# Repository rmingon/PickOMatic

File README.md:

# PickOMatic Motion Controller

Custom motion-control PCB for the PickOMatic pick-and-place toolchain. The board centers on an ATmega2560 (16 MHz) and exposes everything needed to drive the mechanics of a multi-head component placer: coordinated stepper motion, pneumatic handling, lighting, endstop monitoring, and USB connectivity for streaming G-code.

## Repository Layout

- `hardware/` – KiCad 8 project: schematic, PCB, fabrication outputs, and backups.
- `schematic.png` / `pcb.png` / `3D.png` – quick previews of the current design.

Open the KiCad project (`hardware/hardware.kicad_pro`) to inspect or modify the schematic/PCB.

## Hardware Highlights

| Function              | Implementation                                                                                                                             |
| --------------------- | ------------------------------------------------------------------------------------------------------------------------------------------ |
| MCU                   | ATmega2560 @ 16 MHz with a full 5 V I/O bank exposed for motion, sensors, and auxiliary loads.                                             |
| Programming           | Standard 6-pin AVR-ISP header for bootloader bring-up, plus an onboard CH340C USB-UART for firmware uploads and runtime G-code/telemetry.  |
| Axis control          | Five primary stepper channels (2×X, 2×Y, 1×Z) plus two auxiliary stepper channels dedicated to the dual picker heads.                      |
| Vertical compliance   | Three hobby-servo outputs cooperate with the Z axis so each picker head can adjust nozzle height independently (fine pitch vs bulk parts). |
| Pneumatics & lighting | High-side driver for the vacuum/air pump and relay output for the inspection light that assists the vision camera.                         |
| Endstops              | Five limit-switch inputs routed to PCINT lines so firmware can react immediately to any axis stop without polling latency.                 |

## Connectors & Loads

- **Power** – The digital domain remains at 5 V; provide the motor/lighting voltages required by your external drivers (consult the schematic to confirm connector pinouts and allowable current).
- **Steppers** – Eight pairs of STEP/DIR outputs let you interface with typical plug-in drivers (A4988, DRV8825, TMC series). Wire the two X and two Y channels to the corresponding gantry motors so firmware can keep them phase-aligned.
- **Servos** – Three 3-pin headers (signal/5 V/GND) drive standard RC servos for nozzle tilt or compliance adjustments.
- **Vacuum & light** – The pump driver is sized for continuous duty vacuum pumps; the relay contact can switch the illumination supply for the fiducial/alignment camera.
- **Endstops** – Use normally-closed switches whenever possible; the PCINT implementation catches interruptions even while the MCU is servicing other tasks.

Refer to `hardware.kicad_sch` for exact connector references, fuse ratings, and any net labels that tie into your firmware pin map.

## Getting Started

1. **Inspect the PCB** – Open the KiCad design and verify clearances, mounting, and connector orientation against your mechanical assembly.
2. **Assemble & power** – Populate the MCU, CH340C, power regulators, and the motion-control connectors. Bring up the board on a bench supply; check that 5 V and any motor rails stay within tolerance under load.
3. **Flash the bootloader** – Use an AVR ISP (e.g., USBasp, Atmel-ICE) on the 6-pin header:

   ```bash
   avrdude -c usbasp -p m2560 -U flash:w:optiboot_atmega2560.hex
   ```

4. **Deploy firmware** – Upload your motion firmware (Marlin, grbl-Mega, custom G-code interpreter) over the CH340C virtual COM port, typically at 115200 baud.
5. **Verify I/O** – Exercise each stepper, servo, and pneumatic output with low-current loads before connecting the actual actuators. Confirm that every endstop triggers in firmware by manually toggling the switches.
6. **Integrate with the PickOMatic toolchain** – Point your host software (Python scripts, OpenPnP, etc.) at the CH340C serial port and stream G-code or custom motion commands.

## Firmware Notes

- **Stepper pairing** – Configure your firmware so the twin X and Y motors share motion planners but can be trammed independently (use dual endstops or sensorless homing if supported).
- **PCINT handling** – Enable pin-change interrupts for the five limit inputs to guarantee hard-stop reactions regardless of motion planner load.
- **Auxiliary steppers** – Treat the dual picker-head steppers as independent “U” and “V” axes or bind them to tool-change macros to orient the nozzles before pick/place moves.
- **Servo timing** – The ATmega2560 has enough timers to dedicate 50 Hz PWM to the three servos; ensure your firmware does not double-book those timers for other peripherals.
- **Pneumatics & lighting** – Map the pump MOSFET and light relay pins to M-code handlers (e.g., `M8/M9` for vacuum, `M42` for light) so pick/place scripts can toggle them inline.

## ATmega2560 Pin Map

Pad numbers reference the TQFP-100 package used on this board. All mappings come directly from `hardware/hardware.kicad_pcb`.

### Stepper channels

| Channel | STEP pin / pad / net    | DIR pin / pad / net    | Suggested use         |
| ------- | ----------------------- | ---------------------- | --------------------- |
| 1       | PC6 · pin 59 · `STEP_1` | PC7 · pin 60 · `DIR_1` | X gantry, left motor  |
| 2       | PC4 · pin 57 · `STEP_2` | PC5 · pin 58 · `DIR_2` | X gantry, right motor |
| 3       | PC2 · pin 55 · `STEP_3` | PC3 · pin 56 · `DIR_3` | Y gantry, front motor |
| 4       | PC0 · pin 53 · `STEP_4` | PC1 · pin 54 · `DIR_4` | Y gantry, rear motor  |
| 5       | PL5 · pin 40 · `STEP_5` | PL6 · pin 41 · `DIR_5` | Z axis lift           |
| 6       | PL3 · pin 38 · `STEP_6` | PL4 · pin 39 · `DIR_6` | Picker A rotation     |
| 7       | PL1 · pin 36 · `STEP_7` | PL2 · pin 37 · `DIR_7` | Picker B rotation     |

> Firmware can reassign channel roles, but keeping 1–4 for the paired XY screws and 5–7 for the vertical/picker actuators matches the board routing and driver placement.

### Pneumatics, lighting & servos

| Function                  | Port / pad   | Net       | Notes                                              |
| ------------------------- | ------------ | --------- | -------------------------------------------------- |
| Vacuum / air pump relay   | PA7 · pin 71 | `RELAY_1` | Drives MOSFET + relay combo for the pump manifold. |
| Vision light relay        | PA6 · pin 72 | `RELAY_2` | Toggles the inspection/camera light.               |
| Servo 1 (picker A tilt)   | PE5 · pin 7  | `SERVO_1` | Standard 5 V RC servo header.                      |
| Servo 2 (picker B tilt)   | PE4 · pin 6  | `SERVO_2` | Standard 5 V RC servo header.                      |
| Servo 3 (shared Z assist) | PE3 · pin 5  | `SERVO_3` | Use for nozzle height trim or feeder kicker.       |
| Status LED                | PA1 · pin 77 | `LED1`    | Tie to firmware heartbeat.                         |
| Power LED                 | PA0 · pin 78 | `LED2`    | Indicates logic rail alive.                        |

### End-stop inputs (PCINT capable)

| Input   | Port / pad   | Net          |
| ------- | ------------ | ------------ |
| Limit 1 | PJ0 · pin 63 | `END_STOP_1` |
| Limit 2 | PJ1 · pin 64 | `END_STOP_2` |
| Limit 3 | PJ2 · pin 65 | `END_STOP_3` |
| Limit 4 | PJ3 · pin 66 | `END_STOP_4` |
| Limit 5 | PJ4 · pin 67 | `END_STOP_5` |

All five pins sit on the `PCINT` bank, so configure them as pin-change interrupts for immediate homing stops.

### Communications & programming

| Interface         | Port(s) / pad(s)                                    | Net(s)                       | Purpose                                                |
| ----------------- | --------------------------------------------------- | ---------------------------- | ------------------------------------------------------ |
| USB-UART (CH340C) | PE0 pin 2 / PE1 pin 3                               | `RX`, `TX`                   | Primary G-code link and bootloader uploads.            |
| Aux UART1         | PD2 pin 45 / PD3 pin 46                             | `RX1`, `TX1`                 | Spare serial for vision controller or toolchanger.     |
| I²C / TWI         | PD0 pin 43 / PD1 pin 44                             | `SCL`, `SDA`                 | Plug sensors (pressure, temperature, fiducial LEDs).   |
| AVR-ISP / SPI     | PB1 pin 20 / PB2 pin 21 / PB3 pin 22 + RESET pin 30 | `SCK`, `MOSI`, `MISO`, `RST` | 6-pin ISP header for bootloader + in-system debugging. |

### Power, clock & reference

- VCC pins (10, 31, 61, 80, 100) tie to `+5V`; GND pins (11, 32, 62, 81, 99) tie to the main ground plane.
- `XTAL1`/`XTAL2` (pads 34/33) connect to the 16 MHz crystal network.
- `AVCC` (pad 100) shares the 5 V rail; add filtering if you extend the analog front-end.
- `AREF` (pad 98) is left uncommitted—strap it to 5 V through 100 nF if you enable analog conversions.

### Spare I/O for future features

PE2, PE6, PE7, PB0, PA2–PA5, PJ5–PJ7, PG0–PG4, PH0–PH7, and the full PF/PK analog banks are presently unassigned. They are broken out on the MCU but not routed elsewhere, so you can bodge-wire or respin the PCB for feeders, cameras, or sensor arrays without touching the core motion stack.

## Bring-Up Checklist

- Continuity-tested all power rails, especially between USB 5 V and main supply.
- Verified correct orientation of CH340C, crystal, and mini-USB connector.
- Checked that every driver enable pin defaults low (disabled) on reset.
- Confirmed pull-ups on endstop inputs so open switches read as “safe”.
- Logged baseline current draw of the pump and lighting relay to size fuses properly.

## License

This hardware is released under the **CERN Open Hardware Licence v2 (Strongly Reciprocal)**. The complete license text is provided in `LICENSE`; keep it with any derivatives or redistributions and review <https://ohwr.org/project/cernohl/wikis/Documents/CERN-OHL-version-2> for updates.

---

Questions, improvements, or bring-up notes are welcome—open an issue or document your findings so the community can build better pick-and-place rigs together.

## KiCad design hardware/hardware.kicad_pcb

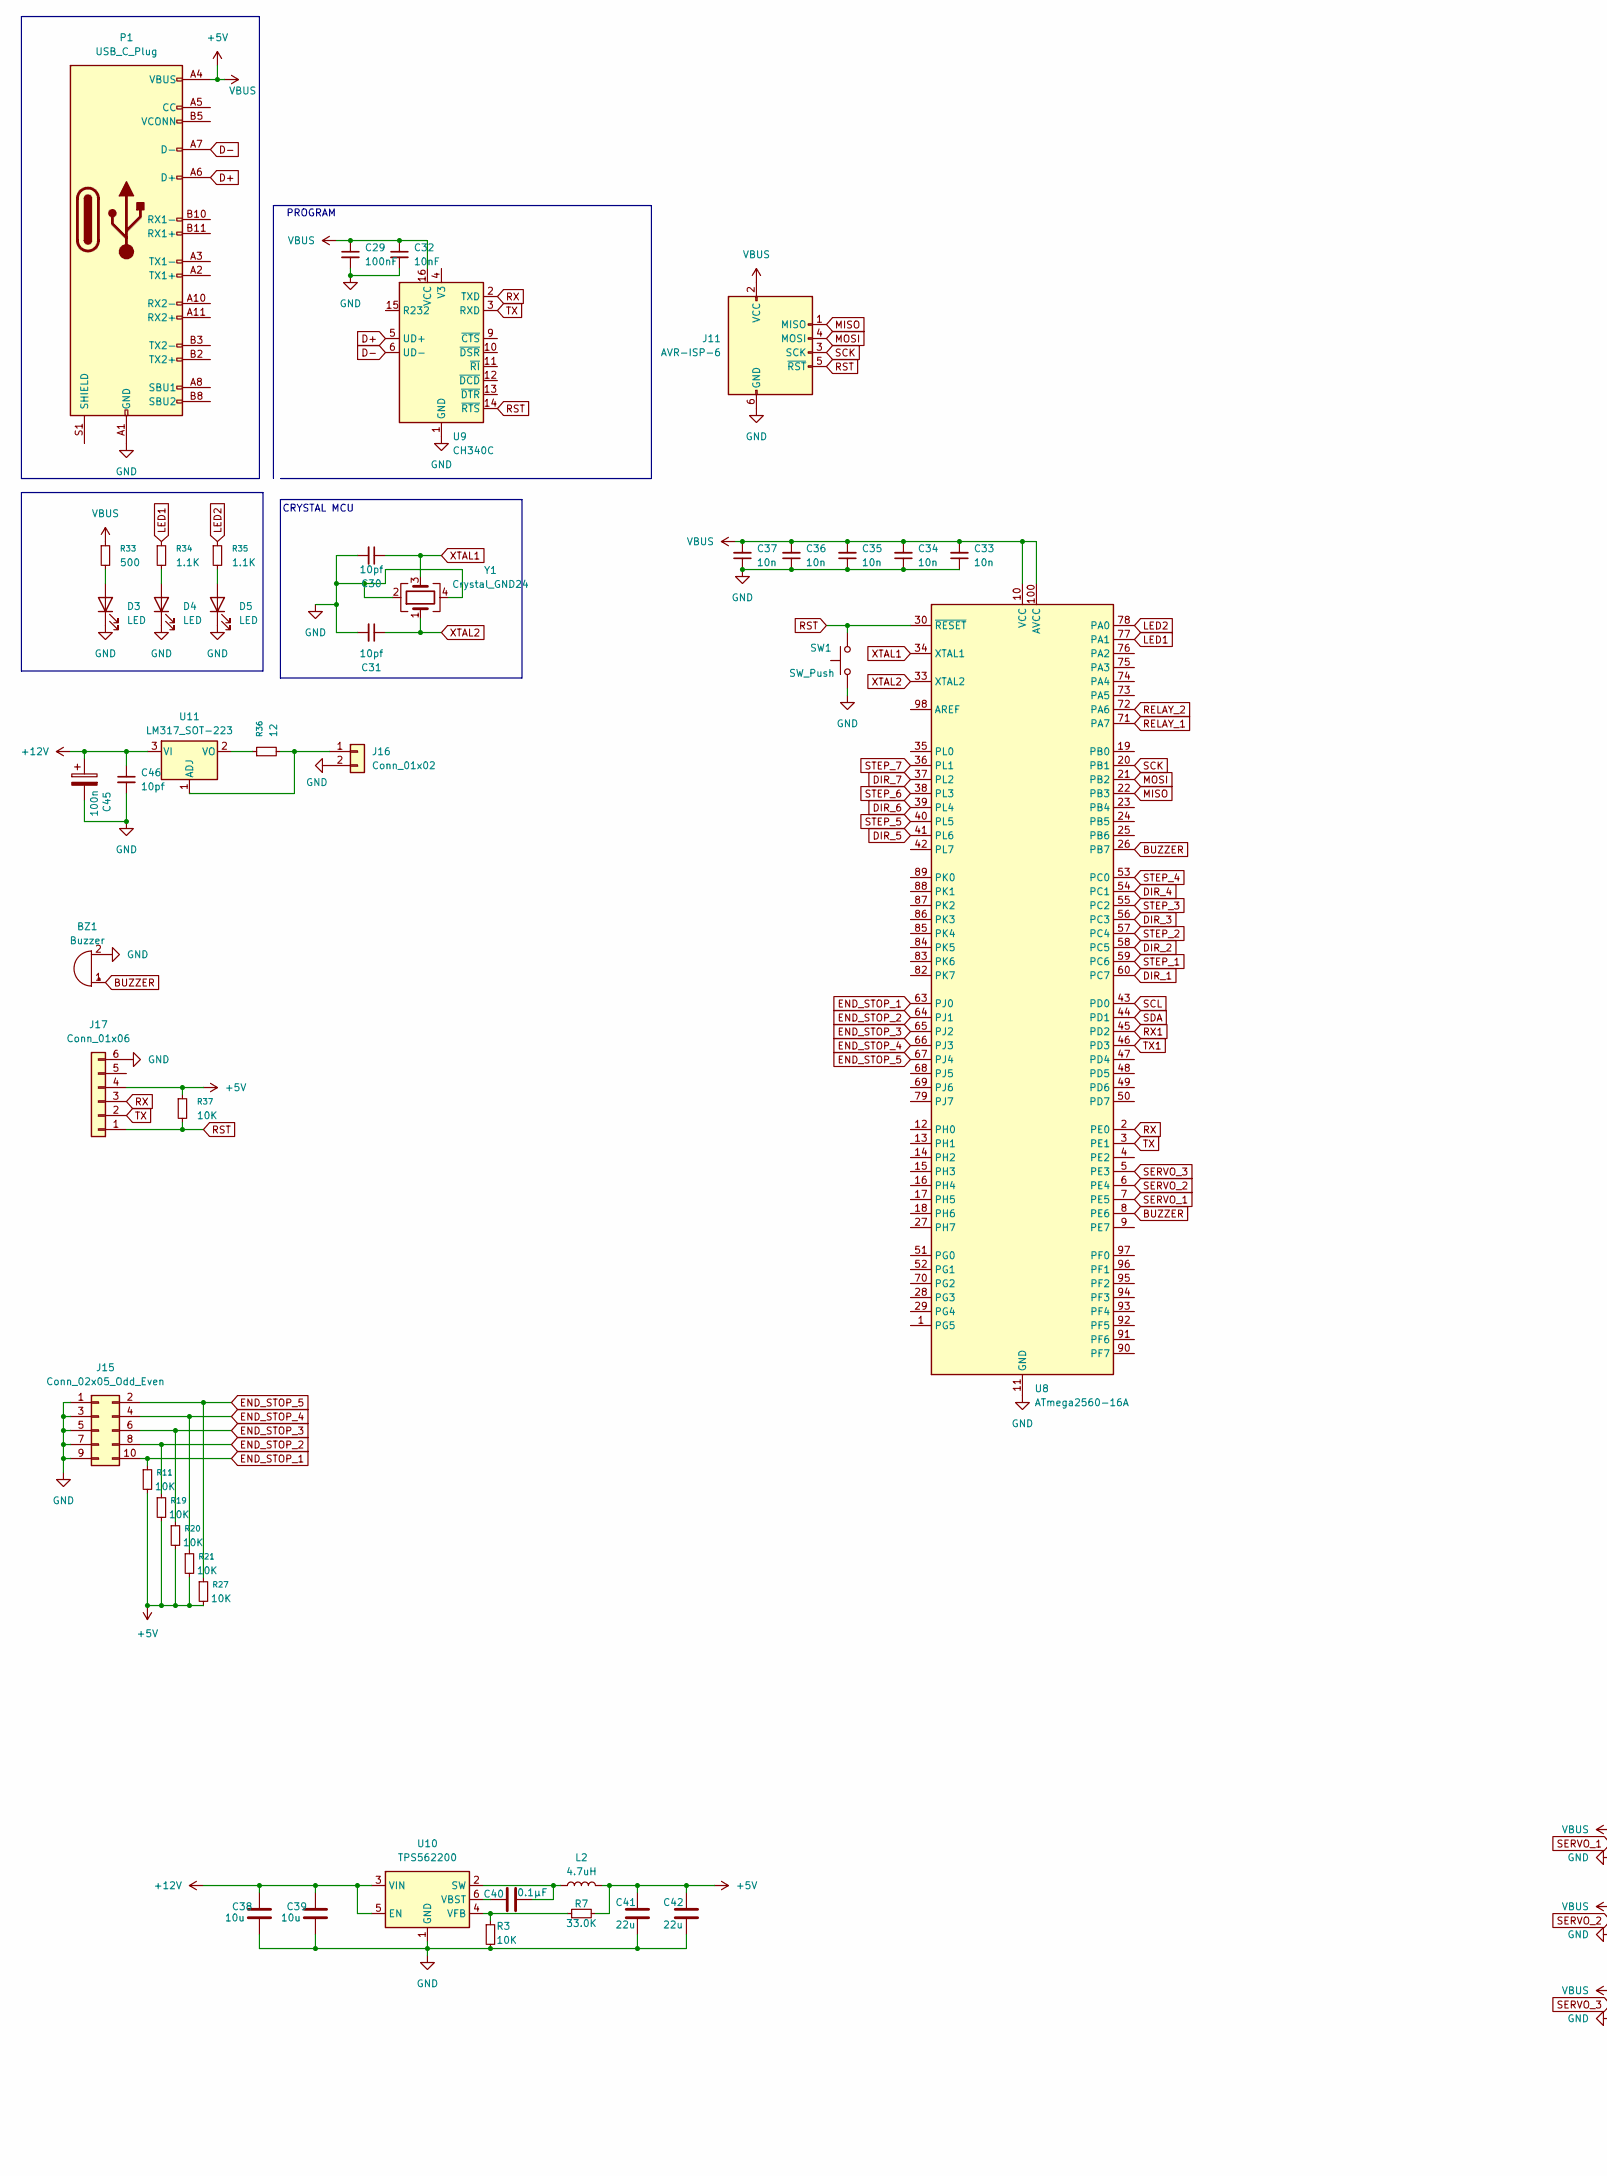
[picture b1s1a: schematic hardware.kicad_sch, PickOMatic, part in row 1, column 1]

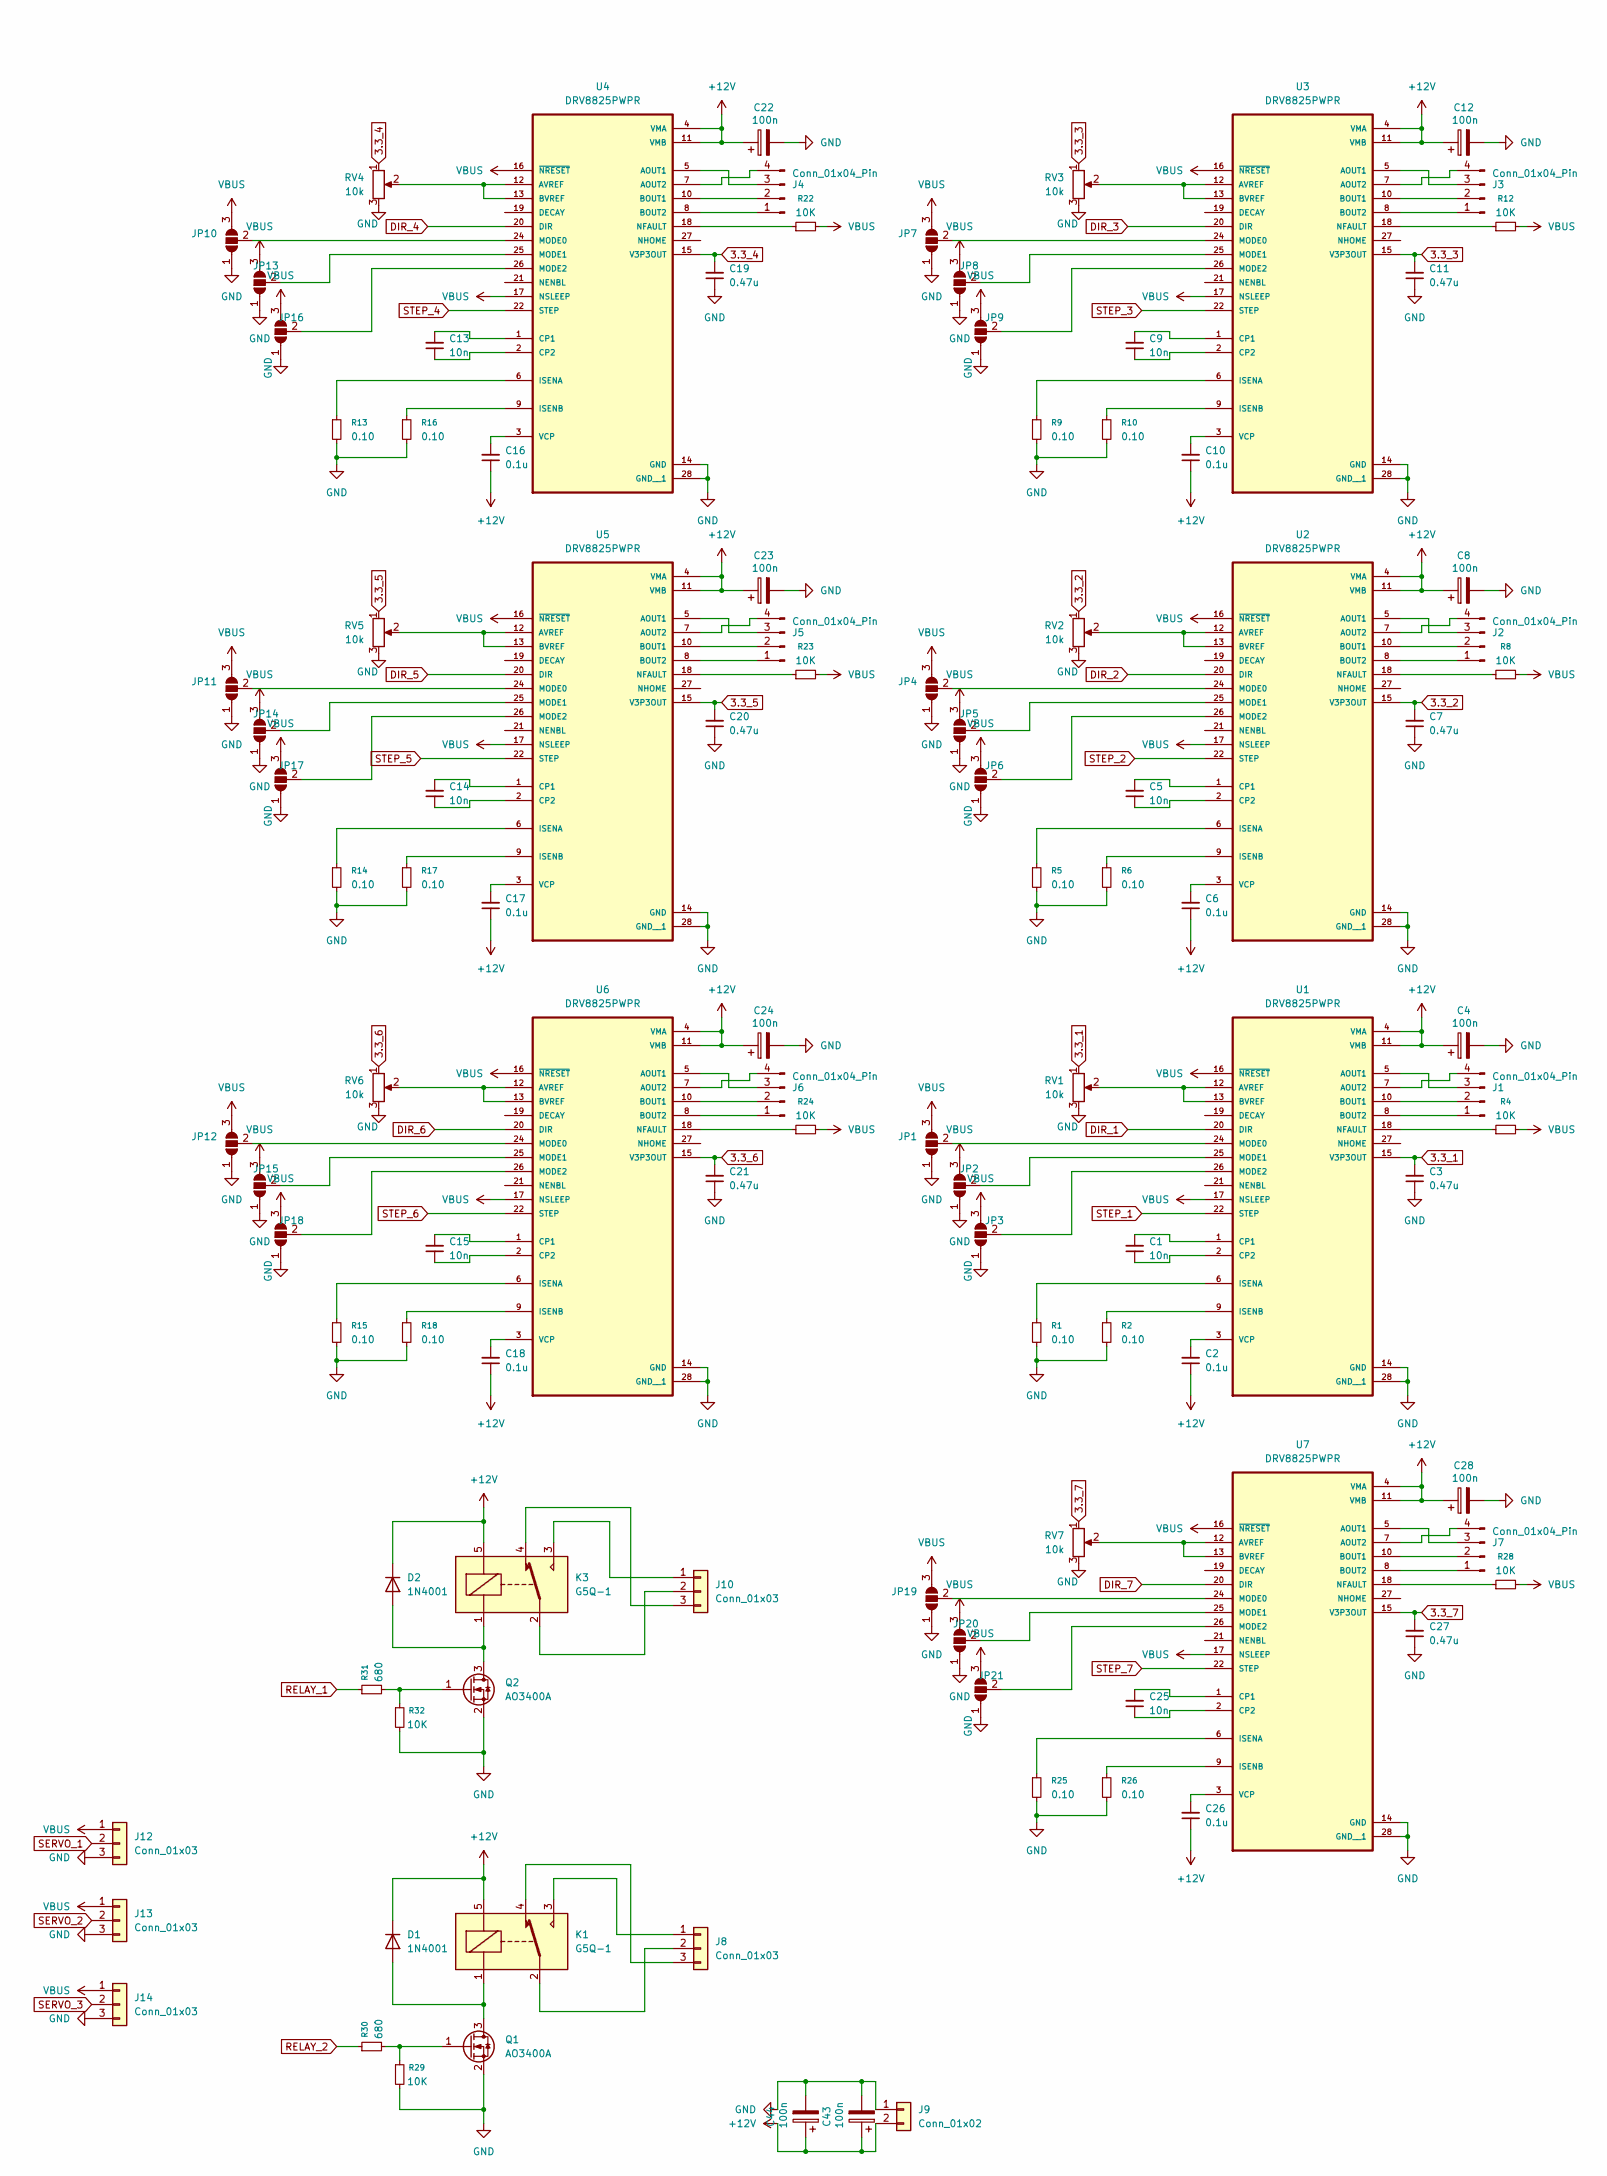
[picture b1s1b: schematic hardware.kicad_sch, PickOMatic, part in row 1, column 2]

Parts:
BZ1: Buzzer; Buzzer_TDK_PS1240P02BT_D12.2mm_H6.5mm
C1, C5, C9, C13, C14, C15, C25, C33, C34, C35, C36, C37: 10n; C_0603_1608Metric
C2, C6, C10, C16, C17, C18, C26: 0.1u; C_0603_1608Metric
C3, C7, C11, C19, C20, C21, C27: 0.47u; C_0603_1608Metric
C4, C8, C12, C22, C23, C24, C28, C43, C44, C45: 100n; CP_Elec_6.3x5.7
C29: 100nF; C_0603_1608Metric
C30, C31, C46: 10pf; C_0603_1608Metric; LCSC C106245
C32: 10nF; C_0603_1608Metric
C38, C39: 10u; C_0603_1608Metric; LCSC C1691
C40: 0.1µF; C_0603_1608Metric; LCSC C6119867
C41, C42: 22u; C_0603_1608Metric; LCSC C6119867
D1, D2: 1N4001; D_DO-41_SOD81_P10.16mm_Horizontal
D3, D4, D5: LED; LED_0603_1608Metric
J1, J2, J3, J4, J5, J6, J7: Conn_01x04_Pin; TerminalBlock_Phoenix_MPT-0,5-4-2.54_1x04_P2.54mm_Horizontal
J8, J10: Conn_01x03; TerminalBlock_TE_282834-3_1x03_P2.54mm_Horizontal
J9: Conn_01x02; TerminalBlock_Phoenix_PT-1,5-2-3.5-H_1x02_P3.50mm_Horizontal
J11: AVR-ISP-6; PinHeader_2x03_P2.54mm_Vertical
J12, J13, J14: Conn_01x03; PinHeader_1x03_P2.54mm_Vertical
J15: Conn_02x05_Odd_Even; PinHeader_2x05_P2.54mm_Vertical
J16: Conn_01x02; Molex_KK-254_AE-6410-02A_1x02_P2.54mm_Vertical
J17: Conn_01x06; PinHeader_1x06_P2.54mm_Vertical
JP1, JP2, JP3, JP4, JP5, JP6, JP7, JP8, JP9, JP10, JP11, JP12, JP13, JP14, JP15, JP16, JP17, JP18, JP19, JP20, JP21: SolderJumper_3_Open; SolderJumper-3_P1.3mm_Open_RoundedPad1.0x1.5mm
K1, K3: G5Q-1; Relay_SPDT_Omron-G5Q-1
L2: 4.7uH; L_Chilisin_BMRA00050520; LCSC C3002619
P1: USB_C_Plug; USB_C_Receptacle_GCT_USB4105-xx-A_16P_TopMnt_Horizontal
Q1, Q2: AO3400A; SOT-23
R1, R2, R5, R6, R9, R10, R13, R14, R15, R16, R17, R18, R25, R26: 0.10; R_0603_1608Metric
R3: 10K; R_0603_1608Metric; LCSC C25804
R4, R8, R11, R12, R19, R20, R21, R22, R23, R24, R27, R28, R29, R32, R37: 10K; R_0603_1608Metric
R7: 33.0K; R_0603_1608Metric; LCSC C4216
R30, R31: 680; R_0603_1608Metric
R33: 500; R_0603_1608Metric
R34, R35: 1.1K; R_0603_1608Metric
R36: 12; R_1206_3216Metric
RV1, RV2, RV3, RV4, RV5, RV6, RV7: 10k; Potentiometer_Bourns_3269W_Vertical
SW1: SW_Push; SW_SPST_CK_RS282G05A3
U1, U2, U3, U4, U5, U6, U7: DRV8825PWPR; IC_TPS61196PWPRQ1
U8: ATmega2560-16A; TQFP-100_14x14mm_P0.5mm
U9: CH340C; SOIC-16_3.9x9.9mm_P1.27mm
U10: TPS562200; SOT-23-6; LCSC C49757
U11: LM317_SOT-223; SOT-223-3_TabPin2
Y1: Crystal_GND24; Crystal_SMD_3225-4Pin_3.2x2.5mm

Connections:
3.3_1: C3.2, RV1.1, U1.15 (V3P3OUT)
3.3_2: C7.2, RV2.1, U2.15 (V3P3OUT)
3.3_3: C11.2, RV3.1, U3.15 (V3P3OUT)
3.3_4: C19.2, RV4.1, U4.15 (V3P3OUT)
3.3_5: C20.2, RV5.1, U5.15 (V3P3OUT)
3.3_6: C21.2, RV6.1, U6.15 (V3P3OUT)
3.3_7: C27.2, RV7.1, U7.15 (V3P3OUT)
+5V: C29.1, C32.1, C33.2, C34.2, C35.2, C36.2, C37.2, C41.1, C42.1, J11.2 (VCC), J12.1, J13.1, J14.1, J17.4, JP1.3 (B), JP2.3 (B), JP3.3 (B), JP4.3 (B), JP5.3 (B), JP6.3 (B), JP7.3 (B), JP8.3 (B), JP9.3 (B), JP10.3 (B), JP11.3 (B), JP12.3 (B), JP13.3 (B), JP14.3 (B), JP15.3 (B), JP16.3 (B), JP17.3 (B), JP18.3 (B), JP19.3 (B), JP20.3 (B), JP21.3 (B), L2.2, P1.A4 (VBUS), P1.A9 (VBUS), P1.B4 (VBUS), P1.B9 (VBUS), R4.2, R7.2, R8.2, R11.2, R12.2, R19.2, R20.2, R21.2, R22.2, R23.2, R24.2, R27.2, R28.2, R33.1, R37.1, U1.16 (~NRESET), U1.17 (NSLEEP), U2.16 (~NRESET), U2.17 (NSLEEP), U3.16 (~NRESET), U3.17 (NSLEEP), U4.16 (~NRESET), U4.17 (NSLEEP), U5.16 (~NRESET), U5.17 (NSLEEP), U6.16 (~NRESET), U6.17 (NSLEEP), U7.16 (~NRESET), U7.17 (NSLEEP), U8.10 (VCC), U8.31 (VCC), U8.61 (VCC), U8.80 (VCC), U8.100 (AVCC), U9.16 (VCC)
+12V: C2.1, C4.1, C6.1, C8.1, C10.1, C12.1, C16.1, C17.1, C18.1, C22.1, C23.1, C24.1, C26.1, C28.1, C38.1, C39.1, C43.1, C44.1, C45.1, C46.1, D1.1 (K), D2.1 (K), J9.2, K1.5, K3.5, U1.4 (VMA), U1.11 (VMB), U2.4 (VMA), U2.11 (VMB), U3.4 (VMA), U3.11 (VMB), U4.4 (VMA), U4.11 (VMB), U5.4 (VMA), U5.11 (VMB), U6.4 (VMA), U6.11 (VMB), U7.4 (VMA), U7.11 (VMB), U10.3 (VIN), U10.5 (EN), U11.3 (VI)
BUZZER: BZ1.1 (+), U8.8 (PE6), U8.26 (PB7)
D+: P1.A6 (D+), U9.5 (UD+)
D-: P1.A7 (D-), U9.6 (UD-)
DIR_1: U1.20 (DIR), U8.60 (PC7)
DIR_2: U2.20 (DIR), U8.58 (PC5)
DIR_3: U3.20 (DIR), U8.56 (PC3)
DIR_4: U4.20 (DIR), U8.54 (PC1)
DIR_5: U5.20 (DIR), U8.41 (PL6)
DIR_6: U6.20 (DIR), U8.39 (PL4)
DIR_7: U7.20 (DIR), U8.37 (PL2)
END_STOP_1: J15.10, R11.1, U8.63 (PJ0)
END_STOP_2: J15.8, R19.1, U8.64 (PJ1)
END_STOP_3: J15.6, R20.1, U8.65 (PJ2)
END_STOP_4: J15.4, R21.1, U8.66 (PJ3)
END_STOP_5: J15.2, R27.1, U8.67 (PJ4)
GND: BZ1.2 (-), C3.1, C4.2, C7.1, C8.2, C11.1, C12.2, C19.1, C20.1, C21.1, C22.2, C23.2, C24.2, C27.1, C28.2, C29.2, C30.2, C31.2, C32.2, C33.1, C34.1, C35.1, C36.1, C37.1, C38.2, C39.2, C41.2, C42.2, C43.2, C44.2, C45.2, C46.2, D3.1 (K), D4.1 (K), D5.1 (K), J9.1, J11.6 (GND), J12.3, J13.3, J14.3, J15.1, J15.3, J15.5, J15.7, J15.9, J16.2, J17.6, JP1.1 (A), JP2.1 (A), JP3.1 (A), JP4.1 (A), JP5.1 (A), JP6.1 (A), JP7.1 (A), JP8.1 (A), JP9.1 (A), JP10.1 (A), JP11.1 (A), JP12.1 (A), JP13.1 (A), JP14.1 (A), JP15.1 (A), JP16.1 (A), JP17.1 (A), JP18.1 (A), JP19.1 (A), JP20.1 (A), JP21.1 (A), P1.A1 (GND), P1.A12 (GND), P1.B1 (GND), P1.B12 (GND), Q1.2 (S), Q2.2 (S), R1.2, R2.2, R3.2, R5.2, R6.2, R9.2, R10.2, R13.2, R14.2, R15.2, R16.2, R17.2, R18.2, R25.2, R26.2, R29.2, R32.2, RV1.3, RV2.3, RV3.3, RV4.3, RV5.3, RV6.3, RV7.3, SW1.1, U1.14 (GND), U1.28 (GND__1), U2.14 (GND), U2.28 (GND__1), U3.14 (GND), U3.28 (GND__1), U4.14 (GND), U4.28 (GND__1), U5.14 (GND), U5.28 (GND__1), U6.14 (GND), U6.28 (GND__1), U7.14 (GND), U7.28 (GND__1), U8.11 (GND), U8.32 (GND), U8.62 (GND), U8.81 (GND), U8.99 (GND), U9.1 (GND), U10.1 (GND), Y1.2, Y1.4; also elsewhere on the board
LED1: R34.1, U8.77 (PA1)
LED2: R35.1, U8.78 (PA0)
MISO: J11.1 (MISO), U8.22 (PB3)
MOSI: J11.4 (MOSI), U8.21 (PB2)
unnamed: D1.2 (A), K1.1, Q1.3 (D)
unnamed: D2.2 (A), K3.1, Q2.3 (D)
unnamed: D3.2 (A), R33.2
unnamed: D4.2 (A), R34.2
unnamed: D5.2 (A), R35.2
unnamed: J1.1, U1.8 (BOUT2)
unnamed: J1.2, U1.10 (BOUT1)
unnamed: J1.3, U1.5 (AOUT1)
unnamed: J1.4, U1.7 (AOUT2)
unnamed: J2.1, U2.8 (BOUT2)
unnamed: J2.2, U2.10 (BOUT1)
unnamed: J2.3, U2.5 (AOUT1)
unnamed: J2.4, U2.7 (AOUT2)
unnamed: J3.1, U3.8 (BOUT2)
unnamed: J3.2, U3.10 (BOUT1)
unnamed: J3.3, U3.5 (AOUT1)
unnamed: J3.4, U3.7 (AOUT2)
unnamed: J4.1, U4.8 (BOUT2)
unnamed: J4.2, U4.10 (BOUT1)
unnamed: J4.3, U4.5 (AOUT1)
unnamed: J4.4, U4.7 (AOUT2)
unnamed: J5.1, U5.8 (BOUT2)
unnamed: J5.2, U5.10 (BOUT1)
unnamed: J5.3, U5.5 (AOUT1)
unnamed: J5.4, U5.7 (AOUT2)
unnamed: J6.1, U6.8 (BOUT2)
unnamed: J6.2, U6.10 (BOUT1)
unnamed: J6.3, U6.5 (AOUT1)
unnamed: J6.4, U6.7 (AOUT2)
unnamed: J7.1, U7.8 (BOUT2)
unnamed: J7.2, U7.10 (BOUT1)
unnamed: J7.3, U7.5 (AOUT1)
unnamed: J7.4, U7.7 (AOUT2)
unnamed: J8.1, K1.3
unnamed: J8.2, K1.2
unnamed: J8.3, K1.4
unnamed: J10.1, K3.3
unnamed: J10.2, K3.2
unnamed: J10.3, K3.4
unnamed: J16.1, R36.2, U11.1 (ADJ)
unnamed: JP1.2 (C), U1.24 (MODE0)
unnamed: JP2.2 (C), U1.25 (MODE1)
unnamed: JP3.2 (C), U1.26 (MODE2)
unnamed: JP4.2 (C), U2.24 (MODE0)
unnamed: JP5.2 (C), U2.25 (MODE1)
unnamed: JP6.2 (C), U2.26 (MODE2)
unnamed: JP7.2 (C), U3.24 (MODE0)
unnamed: JP8.2 (C), U3.25 (MODE1)
unnamed: JP9.2 (C), U3.26 (MODE2)
unnamed: JP10.2 (C), U4.24 (MODE0)
unnamed: JP11.2 (C), U5.24 (MODE0)
unnamed: JP12.2 (C), U6.24 (MODE0)
unnamed: JP13.2 (C), U4.25 (MODE1)
unnamed: JP14.2 (C), U5.25 (MODE1)
unnamed: JP15.2 (C), U6.25 (MODE1)
unnamed: JP16.2 (C), U4.26 (MODE2)
unnamed: JP17.2 (C), U5.26 (MODE2)
unnamed: JP18.2 (C), U6.26 (MODE2)
unnamed: JP19.2 (C), U7.24 (MODE0)
unnamed: JP20.2 (C), U7.25 (MODE1)
unnamed: JP21.2 (C), U7.26 (MODE2)
unnamed: Q1.1 (G), R29.1, R30.2
unnamed: Q2.1 (G), R31.2, R32.1
unnamed: RV1.2, U1.12 (AVREF), U1.13 (BVREF)
unnamed: C1.2, U1.1 (CP1)
unnamed: C1.1, U1.2 (CP2)
unnamed: R1.1, U1.6 (ISENA)
unnamed: R2.1, U1.9 (ISENB)
unnamed: R4.1, U1.18 (NFAULT)
unnamed: C2.2, U1.3 (VCP)
unnamed: RV2.2, U2.12 (AVREF), U2.13 (BVREF)
unnamed: C5.2, U2.1 (CP1)
unnamed: C5.1, U2.2 (CP2)
unnamed: R5.1, U2.6 (ISENA)
unnamed: R6.1, U2.9 (ISENB)
unnamed: R8.1, U2.18 (NFAULT)
unnamed: C6.2, U2.3 (VCP)
unnamed: RV3.2, U3.12 (AVREF), U3.13 (BVREF)
unnamed: C9.2, U3.1 (CP1)
unnamed: C9.1, U3.2 (CP2)
unnamed: R9.1, U3.6 (ISENA)
unnamed: R10.1, U3.9 (ISENB)
unnamed: R12.1, U3.18 (NFAULT)
unnamed: C10.2, U3.3 (VCP)
unnamed: RV4.2, U4.12 (AVREF), U4.13 (BVREF)
unnamed: C13.2, U4.1 (CP1)
unnamed: C13.1, U4.2 (CP2)
unnamed: R13.1, U4.6 (ISENA)
unnamed: R16.1, U4.9 (ISENB)
unnamed: R22.1, U4.18 (NFAULT)
unnamed: C16.2, U4.3 (VCP)
unnamed: RV5.2, U5.12 (AVREF), U5.13 (BVREF)
unnamed: C14.2, U5.1 (CP1)
unnamed: C14.1, U5.2 (CP2)
unnamed: R14.1, U5.6 (ISENA)
unnamed: R17.1, U5.9 (ISENB)
unnamed: R23.1, U5.18 (NFAULT)
unnamed: C17.2, U5.3 (VCP)
unnamed: RV6.2, U6.12 (AVREF), U6.13 (BVREF)
unnamed: C15.2, U6.1 (CP1)
unnamed: C15.1, U6.2 (CP2)
unnamed: R15.1, U6.6 (ISENA)
unnamed: R18.1, U6.9 (ISENB)
unnamed: R24.1, U6.18 (NFAULT)
unnamed: C18.2, U6.3 (VCP)
unnamed: RV7.2, U7.12 (AVREF), U7.13 (BVREF)
unnamed: C25.2, U7.1 (CP1)
unnamed: C25.1, U7.2 (CP2)
unnamed: R25.1, U7.6 (ISENA)
unnamed: R26.1, U7.9 (ISENB)
unnamed: R28.1, U7.18 (NFAULT)
unnamed: C26.2, U7.3 (VCP)
unnamed: C40.2, L2.1, U10.2 (SW)
unnamed: C40.1, U10.6 (VBST)
unnamed: R3.1, R7.1, U10.4 (VFB)
unnamed: R36.1, U11.2 (VO)
RELAY_1: R31.1, U8.71 (PA7)
RELAY_2: R30.1, U8.72 (PA6)
RST: J11.5 (~RST), J17.1, R37.2, SW1.2, U8.30 (~RESET), U9.14 (~RTS); also elsewhere on the board
RX: J17.3, U8.2 (PE0), U9.2 (TXD)
RX1: U8.45 (PD2)
SCK: J11.3 (SCK), U8.20 (PB1)
SCL: U8.43 (PD0)
SDA: U8.44 (PD1)
SERVO_1: J12.2, U8.7 (PE5)
SERVO_2: J13.2, U8.6 (PE4)
SERVO_3: J14.2, U8.5 (PE3)
STEP_1: U1.22 (STEP), U8.59 (PC6)
STEP_2: U2.22 (STEP), U8.57 (PC4)
STEP_3: U3.22 (STEP), U8.55 (PC2)
STEP_4: U4.22 (STEP), U8.53 (PC0)
STEP_5: U5.22 (STEP), U8.40 (PL5)
STEP_6: U6.22 (STEP), U8.38 (PL3)
STEP_7: U7.22 (STEP), U8.36 (PL1)
TX: J17.2, U8.3 (PE1), U9.3 (RXD)
TX1: U8.46 (PD3)
XTAL1: C30.1, U8.34 (XTAL1), Y1.3
XTAL2: C31.1, U8.33 (XTAL2), Y1.1

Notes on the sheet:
PROGRAM
CRYSTAL MCU

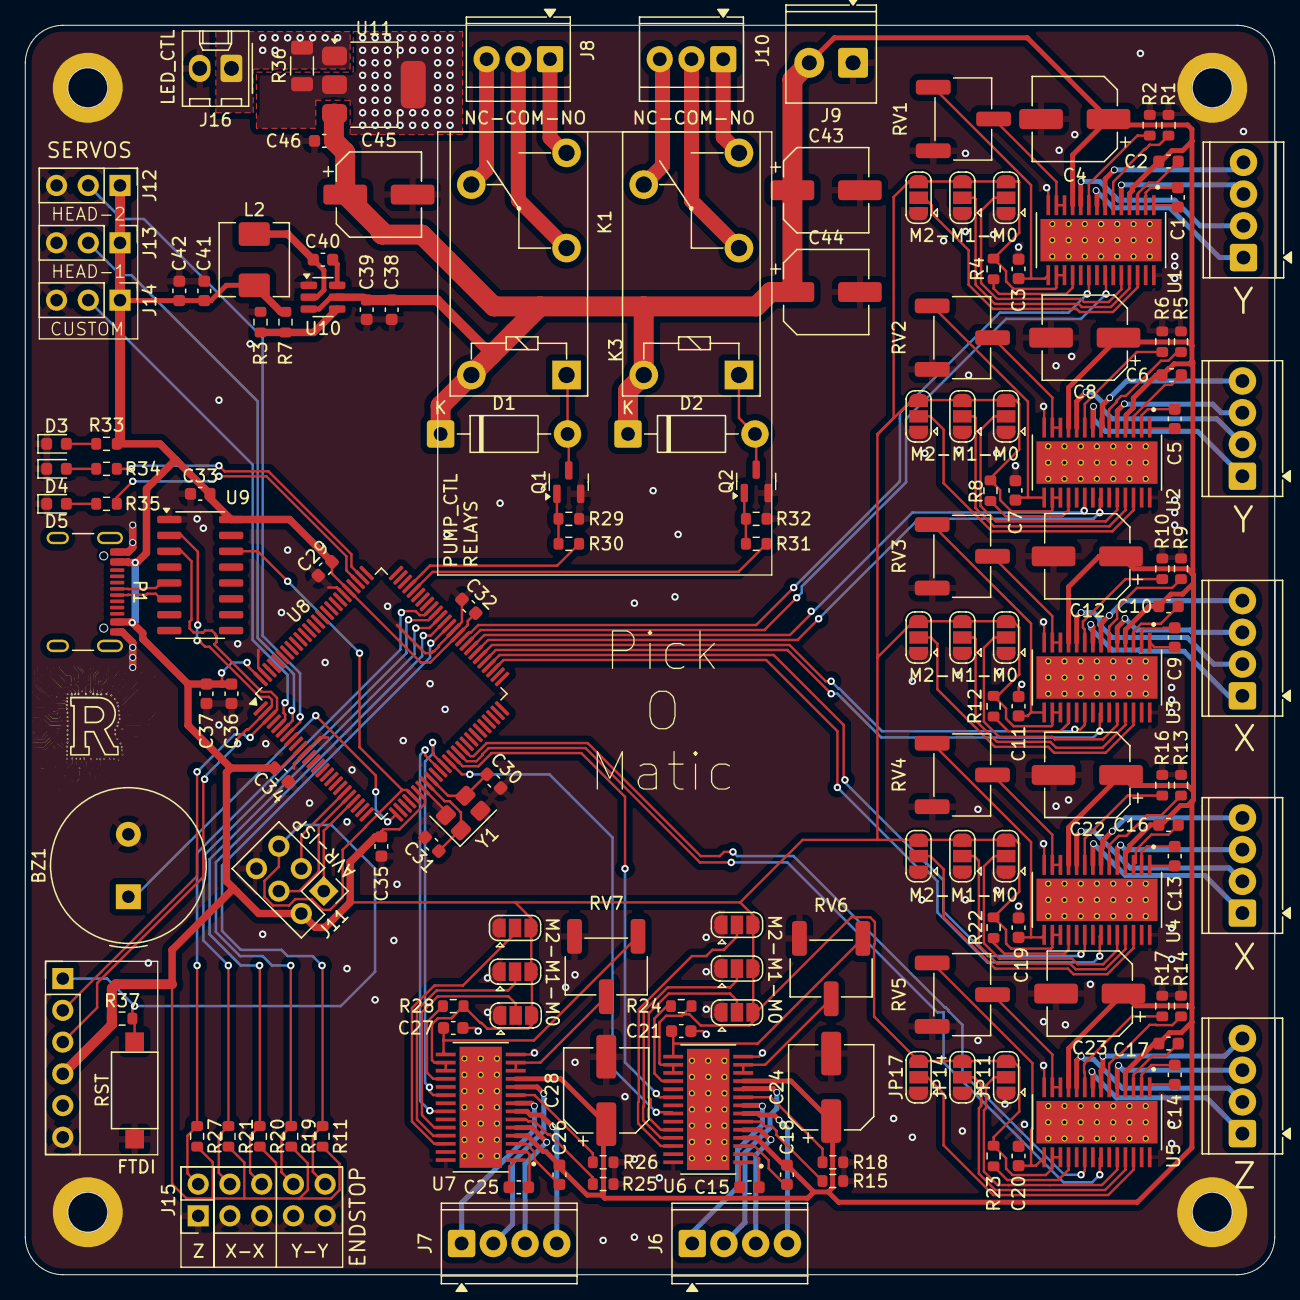
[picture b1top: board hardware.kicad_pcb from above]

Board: 2 copper layers, 100.0 x 100.0 mm, 153 parts (0 on the bottom side), 163 nets.

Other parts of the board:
RST: SW_Push; SW_SPST_CK_RS282G05A3

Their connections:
GND: RST.1; also elsewhere on the board
RST: RST.2; also elsewhere on the board

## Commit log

2025-11-09 add stepper motor schematic
2025-11-09 add relay + mcu schematic
2025-11-09 add connector + uart to usb + avr isp programming schematic
2025-11-09 add pcb and footprints components
2025-11-09 placing relay + drv + edit relay footprints
2025-11-09 wire all drv
2025-11-09 finish pcb wiring
2025-11-09 fix relay +led wiring
2025-11-10 wire current regulator
2025-11-10 finish wiring
2025-11-10 add pictures
2025-11-10 add license + readme
2025-11-10 add view in readme
2025-11-11 add ftdi + buzzer + rst button
